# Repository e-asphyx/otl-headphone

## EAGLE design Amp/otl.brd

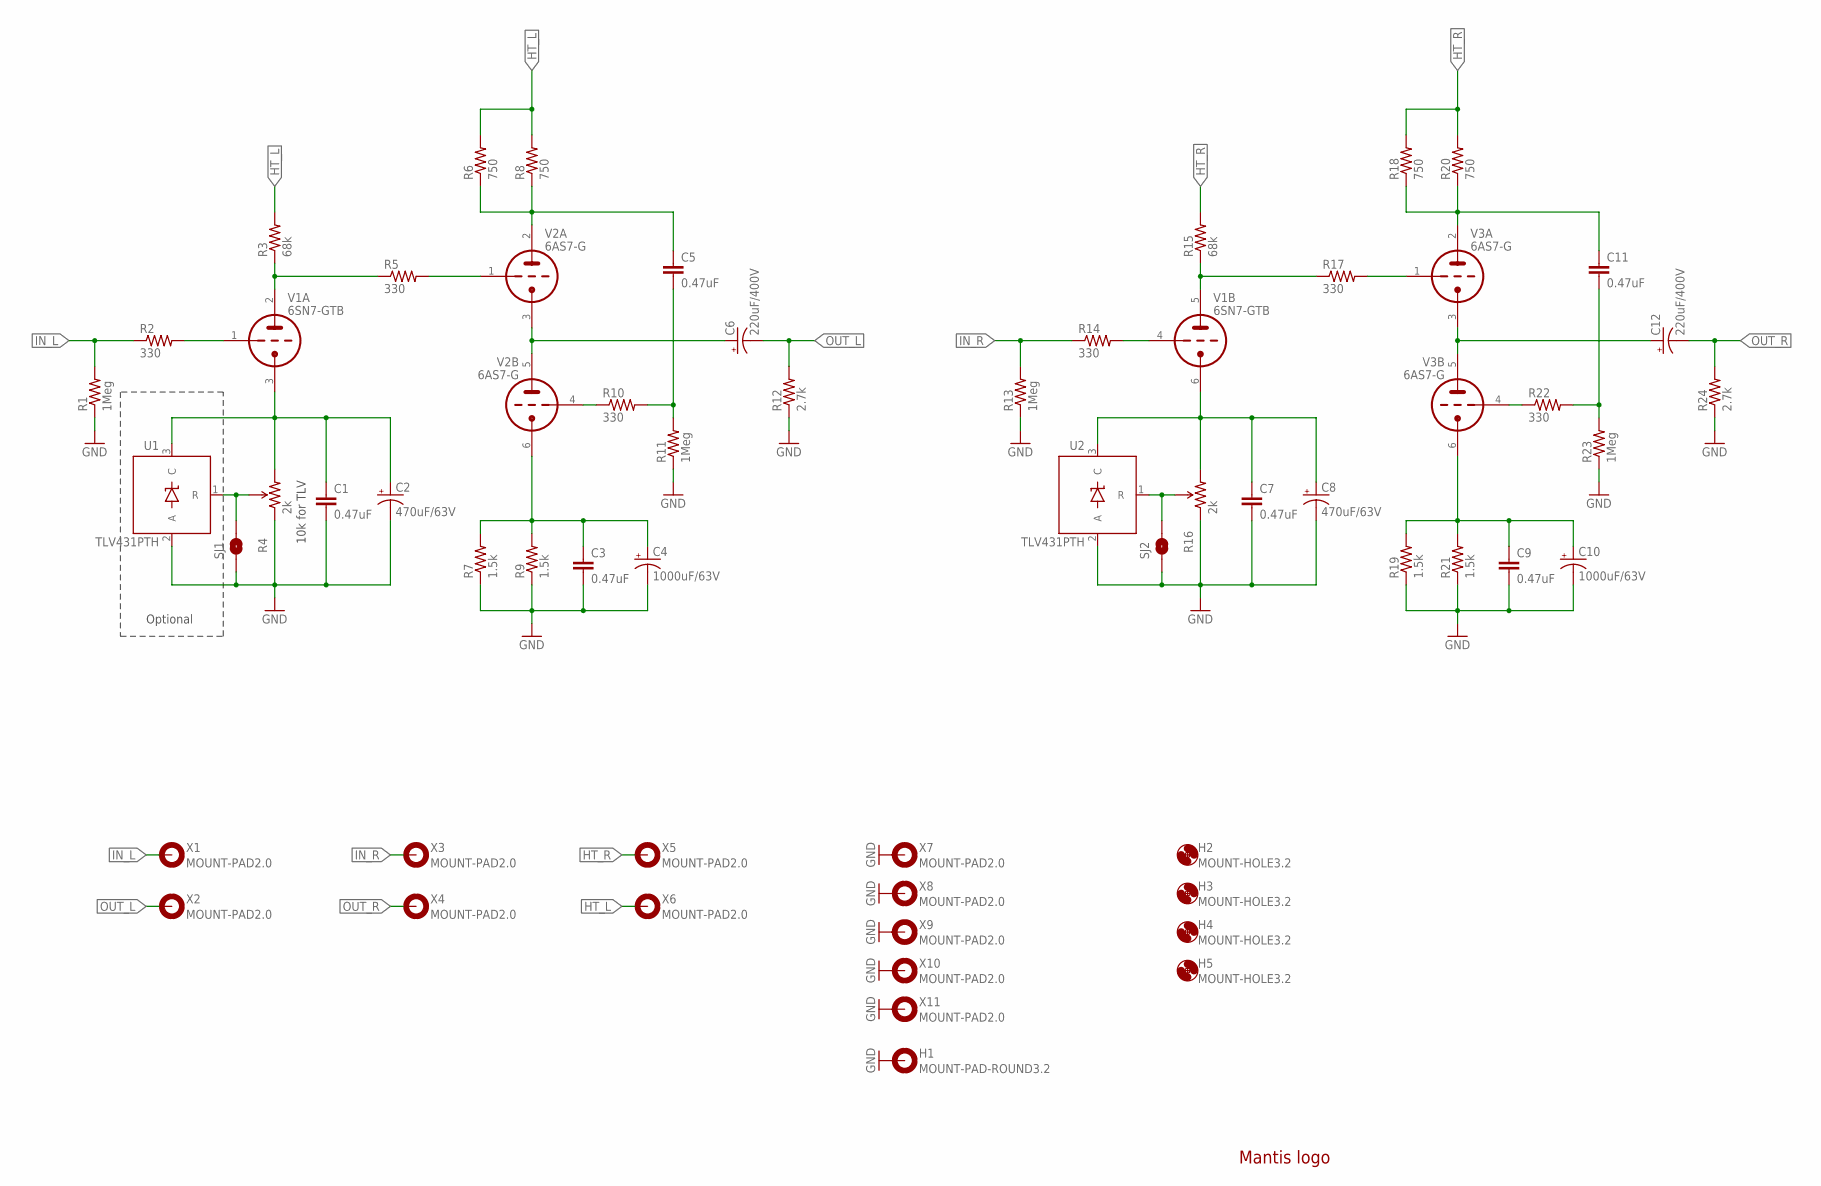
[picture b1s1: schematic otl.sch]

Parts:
C1, C3, C7, C9: 0.47uF; C5B5.5
C2, C8: 470uF/63V; CPOL-RADIAL-16/7.5
C4, C10: 1000uF/63V; CPOL-RADIAL-16/7.5
C5, C11: 0.47uF; C22.5B11
C6, C12: 220uF/400V; CPOL-RADIAL-25/12.5
H1: MOUNT-PAD-ROUND3.2; 3,2-PAD
H2, H3, H4, H5: MOUNT-HOLE3.2; 3,2
LOGO1: LOGO-MANTIS
R1, R11, R13, R23: 1Meg; AXIAL-0.4
R2, R5, R10, R14, R17, R22: 330; AXIAL-0.4
R3, R15: 68k; AXIAL-0.8
R4, R16: 2k; 3362U-2
R6, R8, R18, R20: 750; AXIAL-0.8
R7, R9, R19, R21: 1.5k; AXIAL-0.8
R12, R24: 2.7k; AXIAL-0.4
SJ1, SJ2: SOLDERJUMPERNO-LARGE; SJ_2S-NO-LARGE
U1, U2: TLV431PTH; TO-92
V1: 6SN7-GTB; OKTAL-OUTLET
V2, V3: 6AS7-G; OKTAL-OUTLET
X1, X2, X3, X4, X5, X6, X7, X8, X9, X10, X11: MOUNT-PAD2.0; 2.0-PAD

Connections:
GND: C1.2, C2.2 (-), C3.2, C4.2 (-), C7.2, C8.2 (-), C9.2, C10.2 (-), H1.B3,2, R1.P$1 (1), R4.1 (CCW), R7.P$1 (1), R9.P$1 (1), R11.P$1 (1), R12.P$1 (1), R13.P$1 (1), R16.1 (CCW), R19.P$1 (1), R21.P$1 (1), R23.P$1 (1), R24.P$1 (1), SJ1.1, SJ2.1, U1.2 (A), U2.2 (A), X7.P$1, X8.P$1, X9.P$1, X10.P$1, X11.P$1
HT_L: R3.P$2 (2), R6.P$2 (2), R8.P$2 (2), X6.P$1
HT_R: R15.P$2 (2), R18.P$2 (2), R20.P$2 (2), X5.P$1
IN_L: R1.P$2 (2), R2.P$1 (1), X1.P$1
IN_R: R13.P$2 (2), R14.P$1 (1), X3.P$1
unnamed: C5.1, R6.P$1 (1), R8.P$1 (1), V2.2 (TA)
unnamed: C11.1, R18.P$1 (1), R20.P$1 (1), V3.2 (TA)
unnamed: R10.P$1 (1), V2.4 (TG)
unnamed: C1.1, C2.1 (+), R4.3 (CW), U1.3 (C), V1.3 (TK)
unnamed: C3.1, C4.1 (+), R7.P$2 (2), R9.P$2 (2), V2.6 (TK)
unnamed: C5.2, R10.P$2 (2), R11.P$2 (2)
unnamed: R5.P$2 (2), V2.1 (TG)
unnamed: R3.P$1 (1), R5.P$1 (1), V1.2 (TA)
unnamed: R22.P$1 (1), V3.4 (TG)
unnamed: C6.1 (+), V2.3 (TK), V2.5 (TA)
unnamed: C9.1, C10.1 (+), R19.P$2 (2), R21.P$2 (2), V3.6 (TK)
unnamed: C11.2, R22.P$2 (2), R23.P$2 (2)
unnamed: R17.P$2 (2), V3.1 (TG)
unnamed: R16.2 (WIPER), SJ2.2, U2.1 (R)
unnamed: C7.1, C8.1 (+), R16.3 (CW), U2.3 (C), V1.6 (TK)
unnamed: R15.P$1 (1), R17.P$1 (1), V1.5 (TA)
unnamed: C12.1 (+), V3.3 (TK), V3.5 (TA)
unnamed: R2.P$2 (2), V1.1 (TG)
unnamed: R4.2 (WIPER), SJ1.2, U1.1 (R)
unnamed: R14.P$2 (2), V1.4 (TG)
OUT_L: C6.2 (-), R12.P$2 (2), X2.P$1
OUT_R: C12.2 (-), R24.P$2 (2), X4.P$1

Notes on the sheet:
Optional
10k for TLV

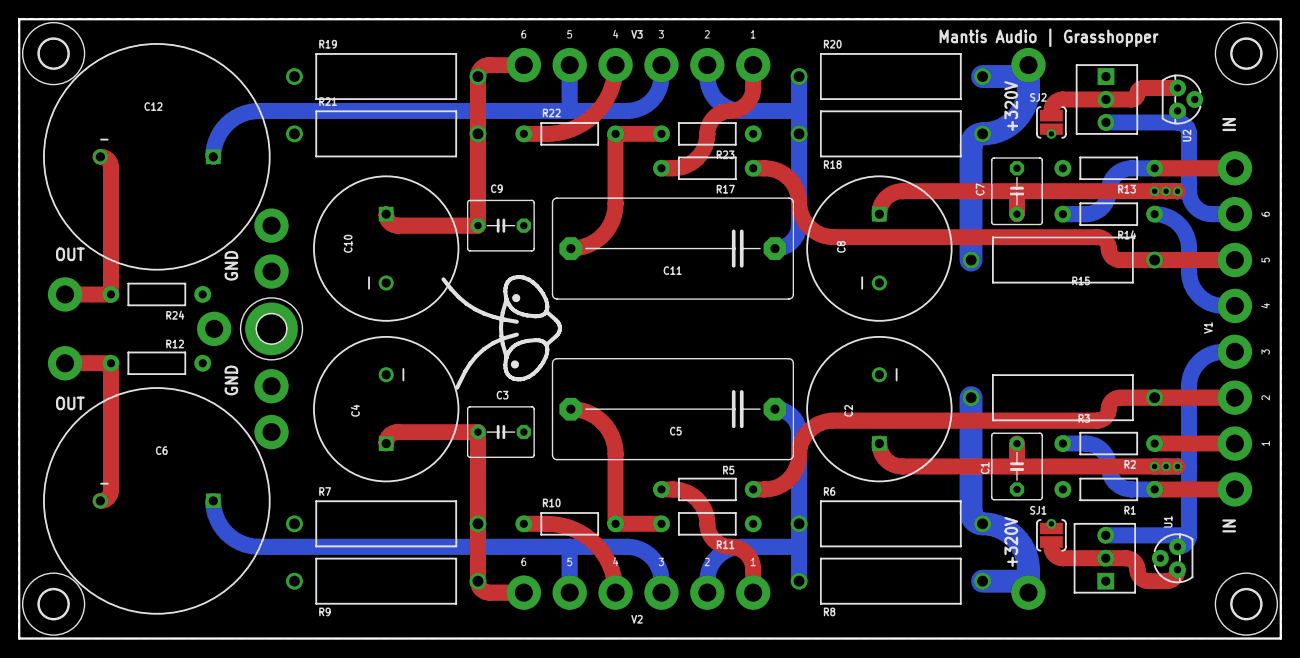
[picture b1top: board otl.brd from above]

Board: 2 copper layers, 139.7 x 68.6 mm, 60 parts (0 on the bottom side), 27 nets.

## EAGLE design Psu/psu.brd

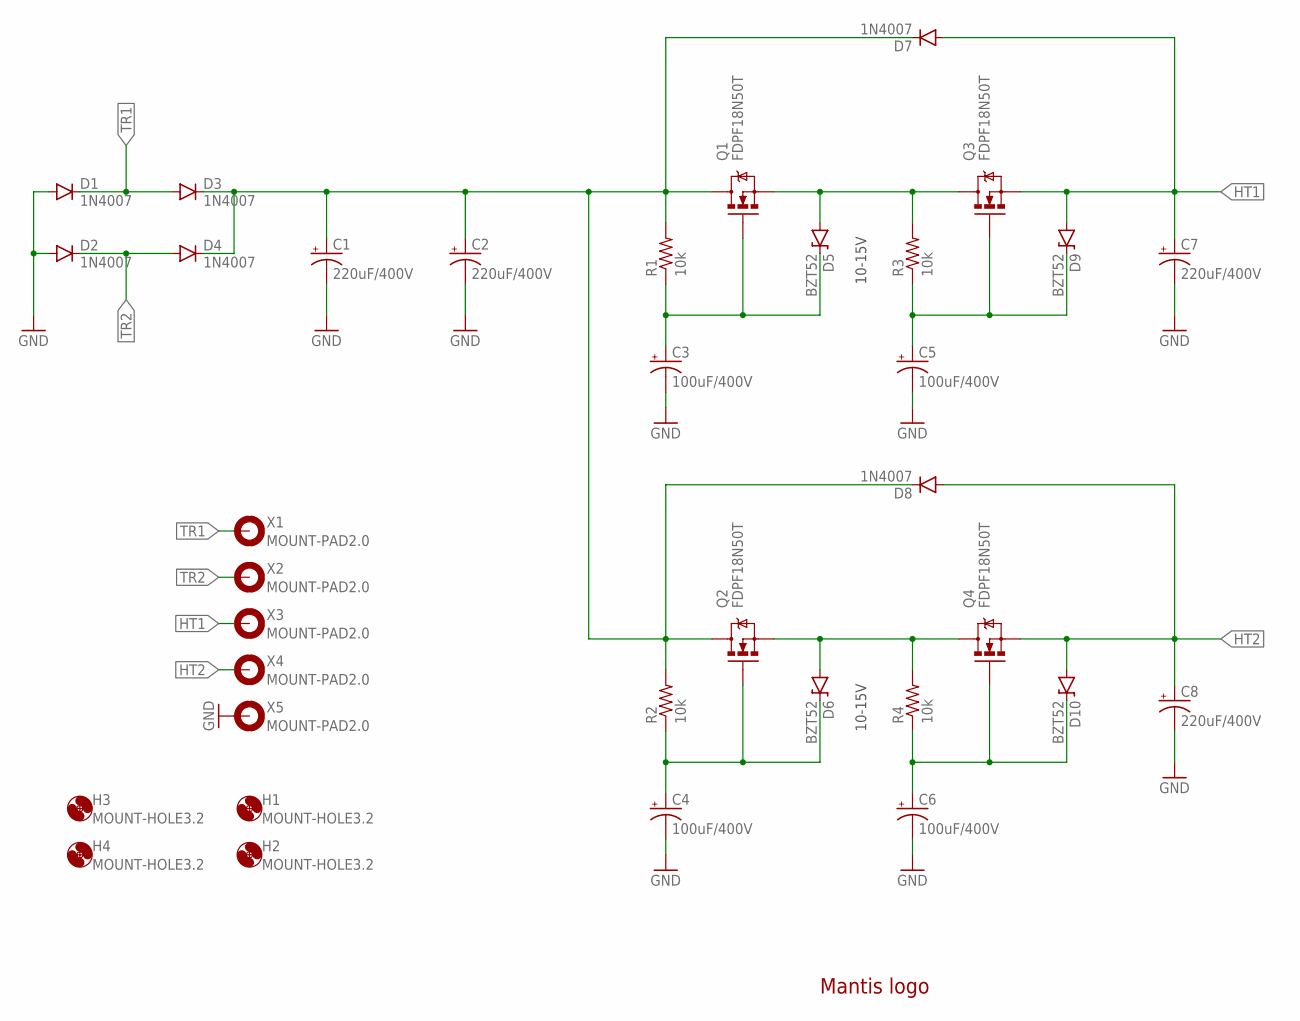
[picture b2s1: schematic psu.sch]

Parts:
C1, C2, C7, C8: 220uF/400V; CPOL-RADIAL-25/12.5
C3, C4, C5, C6: 100uF/400V; CPOL-RADIAL-16/7.5
D1, D2, D3, D4, D7, D8: 1N4007; DIODE-1N4001
D5, D6, D9, D10: BZT52; DIODE-BZT52
H1, H2, H3, H4: MOUNT-HOLE3.2; 3,2
LOGO1: LOGO-MANTIS
Q1, Q2, Q3, Q4: FDPF18N50T; TO220V
R1, R2, R3, R4: 10k; AXIAL-0.4
X1, X2, X3, X4, X5: MOUNT-PAD2.0; 2.0-PAD

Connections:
GND: C1.2 (-), C2.2 (-), C3.2 (-), C4.2 (-), C5.2 (-), C6.2 (-), C7.2 (-), C8.2 (-), D1.A, D2.A, X5.P$1
HT1: C7.1 (+), D7.A, D9.A, Q3.3 (S), X3.P$1
HT2: C8.1 (+), D8.A, D10.A, Q4.3 (S), X4.P$1
unnamed: C1.1 (+), C2.1 (+), D3.C, D4.C, D7.C, D8.C, Q1.2 (D), Q2.2 (D), R1.P$2 (2), R2.P$2 (2)
unnamed: C3.1 (+), D5.C, Q1.1 (G), R1.P$1 (1)
unnamed: D5.A, Q1.3 (S), Q3.2 (D), R3.P$2 (2)
unnamed: C5.1 (+), D9.C, Q3.1 (G), R3.P$1 (1)
unnamed: C4.1 (+), D6.C, Q2.1 (G), R2.P$1 (1)
unnamed: D6.A, Q2.3 (S), Q4.2 (D), R4.P$2 (2)
unnamed: C6.1 (+), D10.C, Q4.1 (G), R4.P$1 (1)
TR1: D1.C, D3.A, X1.P$1
TR2: D2.C, D4.A, X2.P$1

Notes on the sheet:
10-15V

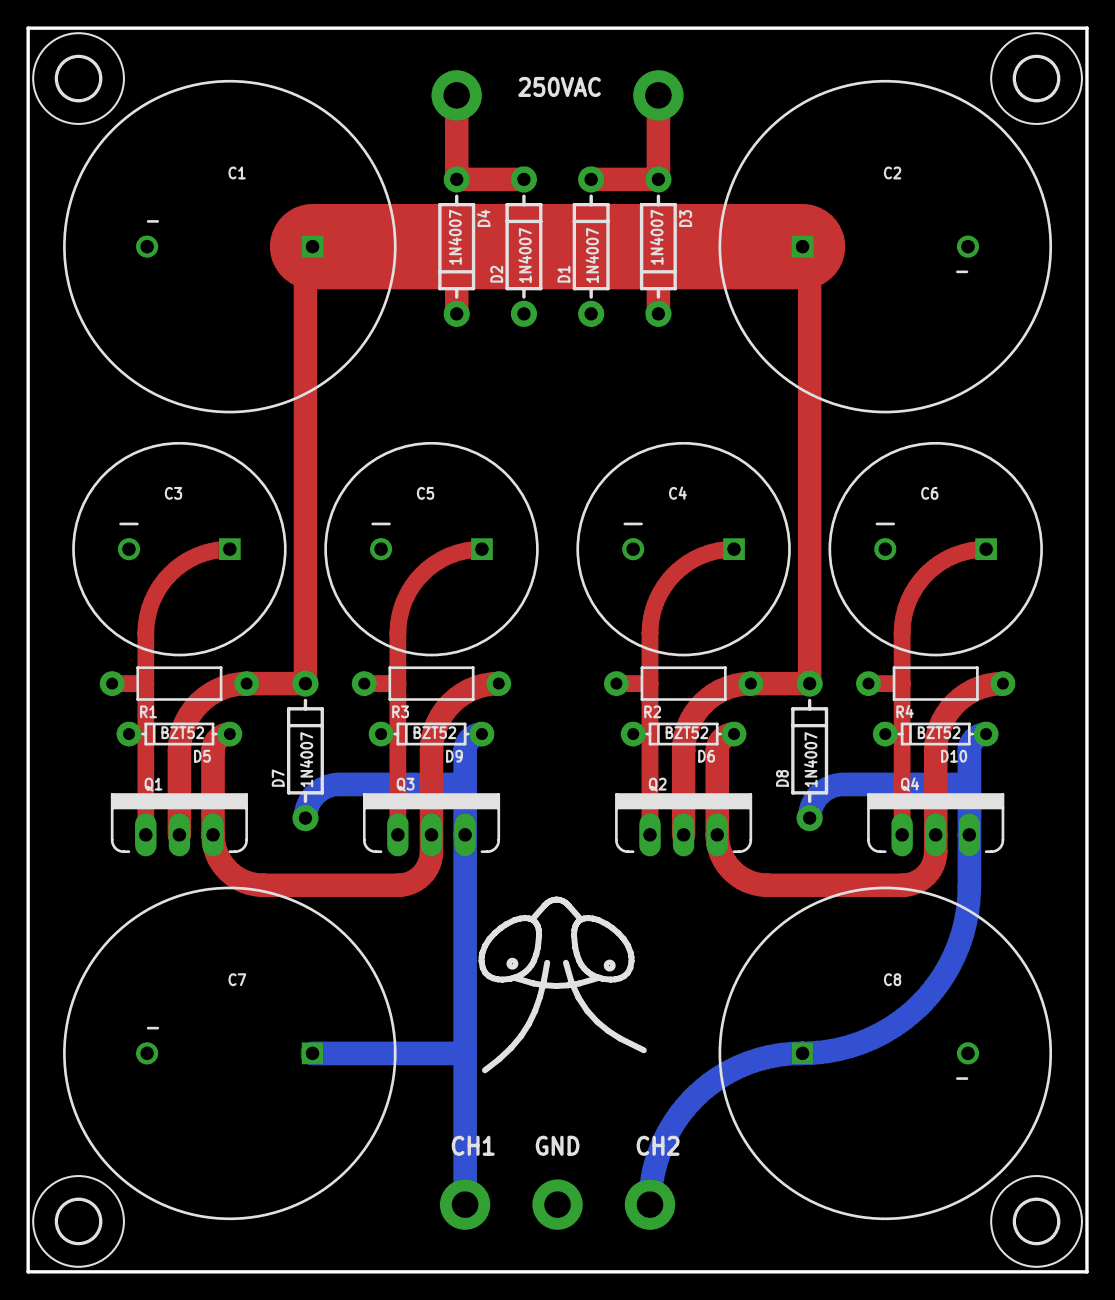
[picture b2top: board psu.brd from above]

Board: 2 copper layers, 80.0 x 94.0 mm, 36 parts (0 on the bottom side), 12 nets.

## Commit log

2016-11-23 Initial
2016-11-23 Power buses separated
2016-11-23 Oops
2016-11-25 Made direct coupled
2016-11-25 Tubes' names added
2016-11-25 More mounting holes
2016-11-27 Small fix

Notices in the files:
parts and their libraries:
SparkFun-Electromechanical: Licensing: Creative Commons ShareAlike 4.0 International - https://creativecommons.org/licenses/by-sa/4.0
